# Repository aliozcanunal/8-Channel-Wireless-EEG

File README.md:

# 8 Channel Wireless EEG

**Installation of Kicad on Ubuntu**

```bash
sudo add-apt-repository --yes ppa:kicad/kicad-5.1-releases

sudo apt update

sudo apt install --install-recommends kicad
```

**After installation;**

```bash
cd ~/Desktop

git clone "https://github.com/aliozcanunal/8-Channel-Wireless-EEG"

kicad eeg.pro
```

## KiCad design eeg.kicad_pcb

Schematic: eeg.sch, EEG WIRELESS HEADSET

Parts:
C1, C20, C104, C105, C109, C110, C114, C115, C119, C120: 10uF; C_0603_1608Metric
C2, C3, C4, C5, C6, C7, C8, C9, C10, C11, C12, C13, C14, C15, C16, C17, C18, C19: 4.7nF; C_0603_1608Metric
C40, C48, C49, C50, C54, C58, C63, C66, C76, C77, C79, C106, C107, C108, C111, C112: 1uF; C_0603_1608Metric
C41, C52, C53, C56, C57, C59, C61, C64, C68, C70, C71, C72, C73, C74, C75, C78: 0.1uF; C_0603_1608Metric
C42: 2.2uF; CP_EIA-1608-08_AVX-J_Pad1.25x1.05mm_HandSolder
C51: 1.5nF; C_0805_2012Metric
C62: 100uF; C_0603_1608Metric
C65: 10uF; RESC3216X65N
C67: 4.7uF; RESC3216X65N
C69: 100uF; RESC3216X65N
C80, C81: 9pF; C_1206_3216Metric
C83: 0.1uF; CP_EIA-1608-08_AVX-J_Pad1.25x1.05mm_HandSolder
C100, C102: 1uF_X5R_0603; CAPC1608X94N
C101, C103: 100nF; CAPC1005X55N
C113, C116, C118: 2.2uF; C_0603_1608Metric
C117: 0.01uF; C_0603_1608Metric
D1, D2, D3, D4, D7: LED; LED_0603_1608Metric
HC7361: 2.048mhz; OSCCC500X320X150N
J1, J2, J3, J4: Conn_01x05_Male; PinHeader_1x05_P2.54mm_Vertical
J5: Conn_01x10; PinHeader_1x10_P1.27mm_Vertical
J6, J7: Conn_01x10_Male; PinSocket_1x10_P2.54mm_Vertical
J10: USB_B_Mini; USB_Micro-B_Molex_47346-0001
L1, L2, L4, L5: 3.3uH; INDC2012X87N
R1, R3, R5, R7, R9, R11, R13, R15, R17, R19: 4.99k; RESC1608X55N
R2, R4, R6, R8, R10, R12, R14, R16, R18: 4.99K; RESC1608X55N
R20, R21, R22: R_Small; R_0603_1608Metric
R26: 10K; R_0603_1608Metric
R27: 1M; RESC2012X60N
R28, R29: 10K; RESC1608X55N
R31: 270; LED_0805_2012Metric
R32: 270; R_0603_1608Metric
SW3: EVQ-Q2K03W
U1: STM32F446RE; LQFP-64_10x10mm_P0.5mm
U2: ADS1299-8CHANNEL; TQFP-64_10x10mm_P0.5mm
U3: LD39050PU33R; SON95P300X300X100-7N; DIGI-KEY_PART_NUMBER 497-8716-1-ND
U4: TPS60403DBVT; SOT95P280X145-5N
U5: TPS73225DBVT; SOT95P280X145-5N
U6: TPS72325DBVT; SOT95P280X145-5N
U12: RN4678-V_RM100; RM100
Y1: 16.00Mhz; Crystal_SMD_5032-4Pin_5.0x3.2mm

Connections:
+2V5: C40.1, C41.1, C49.1, C53.1, C115.1, J2.1, L5.2, U2.19 (AVDD), U2.21 (AVDD), U2.22 (AVDD), U2.54 (AVDD1), U2.56 (AVDD), U2.59 (AVDD)
+3V3: C20.2, C56.2, C57.1, C58.1, C59.2, C61.1, C64.2, C67.1, C71.1, C72.1, C73.1, C74.1, C75.2, C76.1, C77.1, C78.1, C79.1, C102.1, C103.1, HC7361.1 (EN), HC7361.4 (Vdd), J2.3, J4.1, J4.2, R28.2, R29.2, U1.1 (VBAT), U1.12 (VSSA/VREF-), U1.13 (VDDA/VREF+), U1.19 (VDD), U1.32 (VDD), U1.48 (VDD), U1.63 (VSS), U1.64 (VDD), U2.48 (DVDD), U2.50 (DVDD), U3.4 (VOUT), U12.4 (BAT_IN)
+5V: C100.1, C101.1, C104.1, J3.1, J3.2, J3.3, J10.1 (VBUS), L1.1, U3.1 (EN), U3.6 (VIN)
-2V5: C48.2, C50.2, C52.2, C54.2, C62.2, C63.2, C65.2, C66.2, C68.1, C69.2, C70.2, C120.1, J2.2, L4.2, U2.20 (AVSS), U2.23 (AVSS), U2.25 (VREFN), U2.32 (AVSS), U2.53 (AVSS1), U2.57 (AVSS), U2.58 (AVSS)
-5V: C110.1, C116.1, L2.2, U6.2 (IN), U6.3 (EN)
/BIASIN: C1.1, C51.2, R1.2, R27.2, U2.62 (RLDIN), U2.63 (RLDOUT)
/BIASINV: C51.1, J7.1, R27.1, U2.61 (RLDINV)
/CBIAS: J7.2, R1.1
/CIN1N: J6.7, R16.1
/CIN1P: J6.8, R17.1
/CIN2N: J6.5, R14.1
/CIN2P: J6.6, R15.1
/CIN3N: J6.3, R12.1
/CIN3P: J6.4, R13.1
/CIN4N: J6.1, R10.1
/CIN4P: J6.2, R11.1
/CIN5N: J7.9, R8.1
/CIN5P: J7.10, R9.1
/CIN6N: J7.7, R6.1
/CIN6P: J7.8, R7.1
/CIN7N: J7.5, R4.1
/CIN7P: J7.6, R5.1
/CIN8N: J7.3, R2.1
/CIN8P: J7.4, R3.1
/CLK: HC7361.3 (OUT), J5.3, U2.37 (CLK)
/CSRB1: J6.9, R18.1
/CSRB2: J6.10, R19.1
/IN1N: C16.2, R16.2, U2.15 (IN1N)
/IN1P: C17.2, R17.2, U2.16 (IN1P)
/IN2N: C14.2, R14.2, U2.13 (IN2N)
/IN2P: C15.2, R15.2, U2.14 (IN2P)
/IN3N: C12.2, R12.2, U2.11 (IN3N)
/IN3P: C13.2, R13.2, U2.12 (IN3P)
/IN4N: C10.2, R10.2, U2.9 (IN4N)
/IN4P: C11.2, R11.2, U2.10 (IN4P)
/IN5N: C8.1, R8.2, U2.7 (IN5N)
/IN5P: C9.2, R9.2, U2.8 (IN5P)
/IN6N: C6.1, R6.2, U2.5 (IN6N)
/IN6P: C7.2, R7.2, U2.6 (IN6P)
/IN7N: C4.1, R4.2, U2.3 (IN7N)
/IN7P: C5.2, R5.2, U2.4 (IN7P)
/IN8N: C2.1, R2.2, U2.1 (IN8N)
/IN8P: C3.2, R3.2, U2.2 (IN8P)
/RN46CTS: U1.15 (PA1), U12.15 (P1_7/CTS)
/RN46RTS: U1.14 (PA0), U12.17 (P0_0/RTS)
/SRB1: C18.2, R18.2, U2.17 (TESTP_PACE_OUT1)
/SRB2: C19.2, R19.2
/USART6_RX: U1.38 (PC7), U12.23 (TXD)
/USART6_TX: U1.37 (PC6), U12.22 (RXD)
/VCAP3: C50.1, C70.1, U2.55 (VCAP3)
CS: J5.7, U1.50 (PA15), U2.39 (CS)
DRDY: J5.9, U1.51 (PC10), U2.47 (DRDY)
GNDA: C1.2, C2.2, C3.1, C4.2, C5.1, C6.2, C7.1, C8.2, C9.1, C10.1, C11.1, C12.1, C13.1, C14.1, C15.1, C16.1, C17.1, C18.1, C19.1, C20.1, C40.2, C41.2, C42.2, C48.1, C49.2, C52.1, C53.2, C56.1, C57.2, C58.2, C59.1, C61.2, C62.1, C63.1, C64.1, C67.2, C71.2, C72.2, C73.2, C74.2, C75.1, C76.2, C77.2, C78.2, C79.2, C80.2, C81.2, C83.2, C100.2, C101.2, C102.2, C103.2, C104.2, C105.2, C106.2, C108.2, C109.2, C110.2, C111.2, C112.2, C113.2, C114.2, C115.2, C116.2, C117.2, C118.2, C119.2, C120.2, D1.1 (K), HC7361.2 (GND), J1.1, J1.2, J2.4, J2.5, J3.4, J3.5, J4.5, J5.10, J10.5 (GND), J10.6 (Shield), R20.2, R21.2, R22.2, R26.1, SW3.1, SW3.3, U1.18 (VSS), U1.31 (VSS), U1.47 (VSS), U2.31 (RESV1), U2.33 (DGND), U2.41 (DAISY_IN), U2.45 (GPIO3), U2.46 (GPIO4), U2.49 (DGND), U2.51 (DGND), U2.52 (CLKSEL), U2.60 (RLDREF), U3.2 (GND), U3.7 (GND), U4.4 (GND), U5.2 (GND), U6.1 (GND), U12.1 (GND), U12.2 (GND), U12.3 (GND), U12.31 (GND), U12.32 (GND), U12.33 (GND)
MISO: J5.6, U1.56 (PB4), U2.43 (DOUT)
MOSI: J5.5, U1.57 (PB5), U2.34 (DIN)
unnamed: C42.1, U1.30 (VCAP_1)
unnamed: C54.1, U2.30 (VCAP2)
unnamed: C66.1, U2.26 (VCAP4)
unnamed: C69.1, U2.28 (VCAP1)
unnamed: C80.1, U1.6 (PH1-OSC_OUT), Y1.1
unnamed: C81.1, U1.5 (PH0-OSC_IN), Y1.2
unnamed: C83.1, SW3.2, SW3.4, U1.7 (NRST)
unnamed: C105.1, C106.1, C111.1, L1.2, U4.2 (IN), U5.1 (IN), U5.3 (EN)
unnamed: C107.1, U4.5 (CFLY+)
unnamed: C107.2, U4.3 (CFLY-)
unnamed: C108.1, C109.1, L2.1, U4.1 (OUT)
unnamed: C112.1, U5.4 (NR)
unnamed: C113.1, C114.1, L5.1, U5.5 (OUT)
unnamed: C117.1, U6.4 (NR)
unnamed: C118.1, C119.1, L4.1, U6.5 (OUT)
unnamed: D1.2 (A), R32.2
unnamed: D2.1 (K), R20.1
unnamed: D2.2 (A), U1.27 (PB1)
unnamed: D3.1 (K), R21.1
unnamed: D3.2 (A), U1.26 (PB0)
unnamed: D4.1 (K), R22.1
unnamed: D4.2 (A), U1.25 (PC5)
unnamed: D7.1 (K), U12.30 (LED)
unnamed: D7.2 (A), R31.1
unnamed: R26.2, U1.60 (BOOT0)
unnamed: R31.2, U12.6 (LDO33_O), U12.7 (VDD_IO)
unnamed: R32.1, U2.42 (GPIO1)
PWDN: J5.1, R28.1, U1.61 (PB8), U2.35 (PWDN)
RESET: J5.2, R29.1, U1.59 (PB7), U2.36 (RESET)
SCLK: J5.8, U1.55 (PB3), U2.40 (SCLK)
START: J5.4, U1.58 (PB6), U2.38 (START)
SWCLK: J4.4, U1.49 (PA14)
SWDIO: J4.3, U1.46 (PA13)
VREFP: C65.1, C68.2, J1.3, J1.4, J1.5, U2.24 (VREFP)

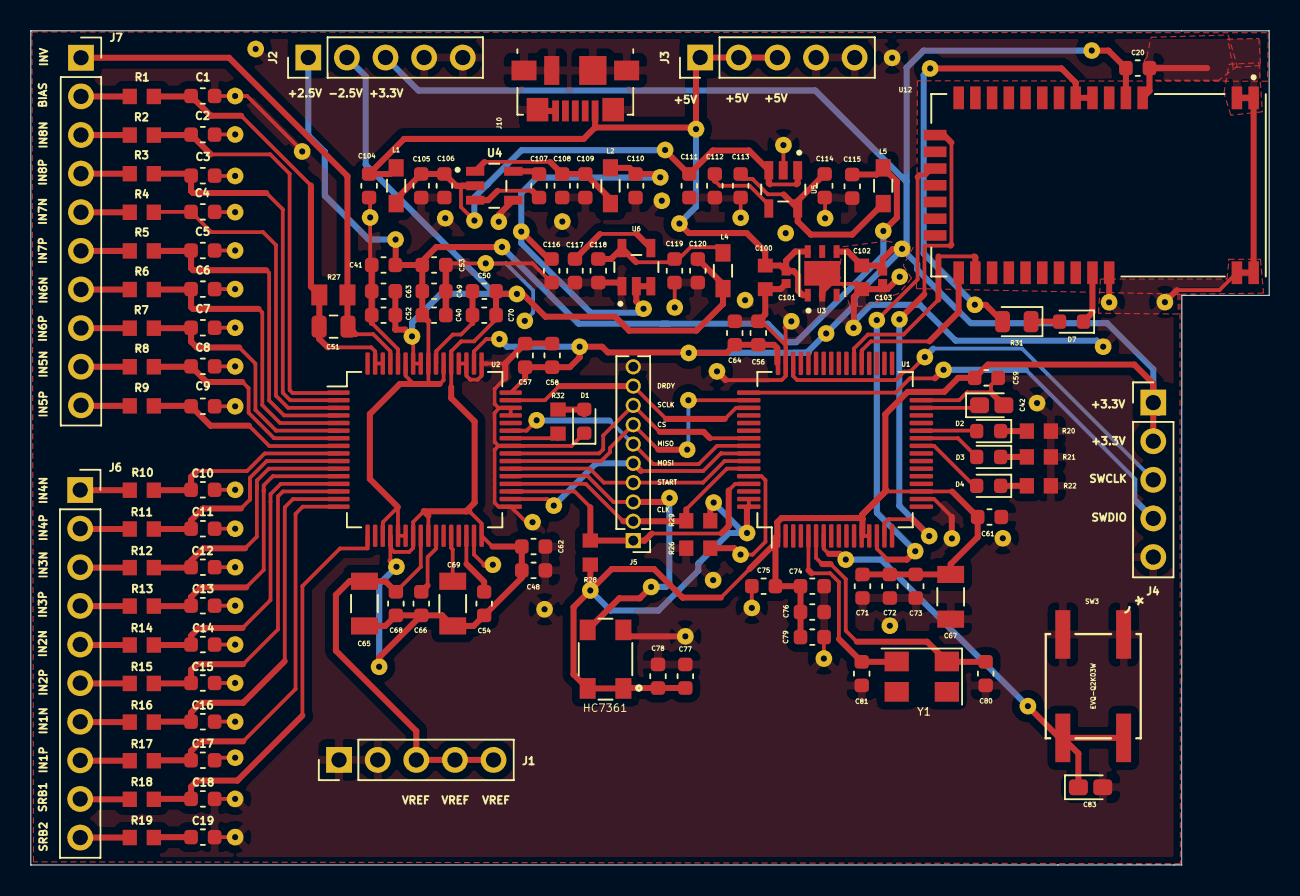
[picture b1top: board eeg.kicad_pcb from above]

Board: 2 copper layers, 81.4 x 54.9 mm, 132 parts (0 on the bottom side), 89 nets.

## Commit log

2020-11-25 Create RN4678 Connections
2020-11-27 fix bluetooth connection and led connection
2020-12-09 RN4678 3D view added
2020-12-10 ERA-3A FOOTPRINT ADDED
2020-12-19 Voltage Regulator Connection Fixed
2020-12-21 Added capacitor footprints redrawed voltage regulators
2020-12-22 ADS1299 Symbol and Footprint Changed, AVDD and ADSS PINS NEED TO FIX
2020-12-22 Footprints edited and aligned
2020-12-24 Added no connection flags
2020-12-25 Electrodes footprint 2.54mm to 1.27mm
2020-12-25 Electrodes pins are need to change
2020-12-26 Electrode1 and electrode2 schematics are fixed
2020-12-27 ADS1299's SPI connections fixed and Supply pins should be checked
2020-12-27 RC connections realigned
2020-12-27 Net file created
2020-12-27 Electrode schematic and footprint redesigned and add library
2021-01-23 ADS1299 Tracks fixed.
2021-02-20 Created hierarchical sheet
2021-02-20 Electrode connections are completed
2021-02-26 GND changed to GNDA
2021-02-26 VCAP capacitors are placed
2021-02-26 AVDD and AVSS capacitors are placed
2021-02-26 uC status leds added
2021-02-26 deleted USB.sch-bak
2021-02-26 Version 0.01.png
2021-02-28 SPI3 changed to SPI1
2021-02-28 EVQ Tactile Button footprint changed
2021-04-29 Gerfer files updated
2021-04-29 Updated 3D view
2021-04-29 Connectors change 1.27mm to 2.54mm and 20 pins to 10 pins
2021-04-29 Via sizes changed 04mm to 1.2mm and bugs fixed
2021-04-29 Net File updated
2021-04-29 bugs fixed
2021-04-29 Voltage Regulators module changed
2021-04-29 F446RE module changed
2021-04-29 cache
2021-05-20 ground tracks removed
2021-05-24 vias changed to pad
2021-05-24 Vias need to change (again)
2021-06-01 RN4678's mode switch added
2021-06-01 RN4678's SW_BTN added
2021-06-01 update sch
